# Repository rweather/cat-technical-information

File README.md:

Technical Information for the Dick Smith Cat / Laser 3000
=========================================================

This project was born out of nostalgia for the 6502-based "Dick Smith Cat"
computer that I had back in the 1980's.  It was mostly Apple II compatible;
overseas it was known as the VTech Laser 3000.  See **History** below for more.

Unfortunately the power supply died on mine and I sent it to the dump.
I now really wish I hadn't!  Fortunately, I did find a Cat on Gumtree
for sale in 2024 and so I now have a Cat again, together with some
accessories (joysticks, disk controller, disk drive, and emulator cartridge).

This project is my contribution to preserving Cat history.

## Schematics

The schematics in the original [Technical Reference Manual](https://archive.org/details/dsecattrm)
are very hard to read.  So I decided to redraw them in KiCad.

There are lots of details missing in the Technical Reference Manual;
for example, U17 is listed in the schematic but there is no information
that it is a 74LS86 Quad XOR gate.  It was necessary to figure out
from context what the components were.  I'll cross-check them with the
actual Cat later.

Here are the schematics, redrawn in Kicad:

* [Motherboard Schematic](schematics/Dick_Smith_Cat_Motherboard/PDF/Dick_Smith_Cat_Motherboard.pdf)
* [PAL Linear Board Schematic](schematics/Dick_Smith_Cat_Linear_Board_PAL/PDF/Dick_Smith_Cat_Linear_Board_PAL.pdf)
* [Power Supply Schematic](schematics/Dick_Smith_Cat_Power_Supply/PDF/Dick_Smith_Cat_Power_Supply.pdf)
* [Emulator Cartridge Schematic](schematics/Dick_Smith_Cat_Emulator/PDF/Dick_Smith_Cat_Emulator.pdf)
* [Joystick Schematic](schematics/Dick_Smith_Cat_Joysticks/PDF/Dick_Smith_Cat_Joysticks.pdf)

## Kernel ROM Listing

I have typed up the kernel ROM listing from the Technical Reference Manual,
and annotated it with my own notes as to what is happening.  The source
code can be found in the [src/kernel](src/kernel) directory.

## Memory Map

The Cat supports an 18-bit 256K memory address space, divided up into
sixteen 16K memory banks.  Any of these sixteen memory banks can be
mapped into four memory "windows" at addresses $0000, $4000, $8000, and
$C000.  By default the ROM maps memory banks 0, 1, 3, and F into the
four memory windows.

* $00000 to $0FFFF - 64K of RAM on the motherboard.
* $10000 to $2FFFF - 128K of expansion RAM (not fitted as standard).
* $30000 to $37FFF - Unused space.
* $38000 to $3BFFF - BASIC ROM.
* $3C000 to $3CFFF - I/O space.
* $3D000 to $3FFFF - BASIC and kernel monitor ROM.

The memory windows are set by writing the memory bank number (0-F) to the
I/O addresses $3C07C, $3C07D, $3C07E, and $3C07F.  The memory bank numbers
should also be written to zero page locations $C5, $C6, $C7, and $C8
so that the rest of the system knows the current memory arrangement.

Note: Writing a value other than F to $3C07F will make the system unusable
as the I/O space will become inaccessible in the 6502's 64K address space.
There is no way to restore the correct mapping except via a system reset.

## Slots

The Cat does not have physical slots in the same sense as the Apple II.
The 72-pin expansion connectors have the entire 256K 18-bit address bus and
8-bit data bus available.  Decoding of slot addresses is done on the plug-in
cartridges.  The I/O "slots" are virtual and are allocated as follows:

* Slot 0 - Emulator cartridge a.k.a the language card
* Slot 1 - Printer
* Slot 2 - RS-232
* Slot 3 - 80 column mode
* Slot 4 - Unused
* Slot 5 - Reserved for a second disk controller
* Slot 6 - Standard disk controller
* Slot 7 - Unused

At startup, the monitor ROM will probe for a disk controller in slot 6
and then the ROM will probe for a disk controller in slot 5.  If either
slot is occupied, the ROM jumps to the disk controller's ROM to boot
from the external disk drive.

Cat's didn't use slot 5 - the disk controller was always in slot 6.

Slot 5 could be used to create a bootable game or program cartridge.
Instead of booting a disk, the program in the cartridge is run
automatically at power on if there is no disk constroller cartridge
present.  The following hexadecimal bytes should appear at $C500 to
make the cartridge auto-boot:

    A2 20 A0 00 A2 03 86 3C

These signature bytes are followed by code to load the cartridge's ROM
contents into main RAM to run the program.  Or bank-switch in the
cartridge at address $4000 or $8000 to execute directly out of the ROM.

If a disk controller cartridge is present in slot 6, then slot 5 will not
boot automatically.  Use <tt>PR#5</tt> at the BASIC prompt to activate the
code in the slot 5 cartridge.

## New Projects

* [ROM cartridge for the RS-232 interface](ROMCart.md)

## Can We Rebuild It?

Since Cats (and Laser 3000's) are so rare these days, there is a question as
to whether we could build a replica using modern off-the-shelf parts.

Well, no.

The core of the Cat is two 64-pin gate array chips, U2 and U14.  These
handle glue logic, dynamic RAM interfacing, and the video subsystem.
Without a working Cat to harvest the chips from, there's no way to replicate it.
And if I have a working Cat, I don't need to replicate it!

The gate arrays and clean-roomed ROM's is how VTech avoided Apple's lawyers.
It wasn't a chip for chip rip-off of the Apple II like many other clones
back in the day.

In theory a new circuit could be built using the equivalent in TTL logic
chips, but then you'd end up with a straight Apple II clone.  There are
plenty of designs online for that, including the original Apple II schematics.

The other possibility is to use a modern FPGA to replicate the original
gate arrays on 64-pin carrier boards.  That would be useful for repairing
actual Cats, but would be a lot of work.

Another problem for replication is the ROM's.  The assembly code for the
kernel monitor ROM is in the Technical Reference Manual.  I have put the
code in the [src/kernel](src/kernel) sub-directory of this repository,
annotated with some of my own notes to explain what is going on.

I wasn't been able to find the BASIC ROM's online anywhere.  I had bits and
pieces of the BASIC ROM's that I disassembled by hand back in the day,
but not a complete set.  Now that I have a working Cat, I will dump the
ROM's at some point.

## Chip List

As mentioned above, the schematics in the Technical Reference Manual do not
include information as to what part each "Un" designator corresponds to.
Most of them I was able to figure out from context and the rest were
confirmed through inspection of an actual Cat motherboard.

<table border="1">
<tr><td><b>Designator</b></td><td><b>Part</b></td><td><b>Schematic Pages</b></td></tr>
<tr><td>U1</td><td>555 Timer</td><td>2</td></tr>
<tr><td>U2</td><td>Gate Array 2</td><td>4</td></tr>
<tr><td>U3</td><td>74LS04 Hex Inverter</td><td>4</td></tr>
<tr><td>U4</td><td>74LS04 Hex Inverter</td><td>2, 4, 7</td></tr>
<tr><td>U5</td><td>4164 64-kbit Dynamic RAM</td><td>5</td></tr>
<tr><td>U6</td><td>4164 64-kbit Dynamic RAM</td><td>5</td></tr>
<tr><td>U7</td><td>4164 64-kbit Dynamic RAM</td><td>5</td></tr>
<tr><td>U8</td><td>4164 64-kbit Dynamic RAM</td><td>5</td></tr>
<tr><td>U9</td><td>4164 64-kbit Dynamic RAM</td><td>5</td></tr>
<tr><td>U10</td><td>4164 64-kbit Dynamic RAM</td><td>5</td></tr>
<tr><td>U11</td><td>4164 64-kbit Dynamic RAM</td><td>5</td></tr>
<tr><td>U12</td><td>4164 64-kbit Dynamic RAM</td><td>5</td></tr>
<tr><td>U13</td><td>74LS174 Hex D-Type Flip-Flop (some boards fit a 74LS244 instead for U13)</td><td>4</td></tr>
<tr><td>U14</td><td>Gate Array 1</td><td>4</td></tr>
<tr><td>U15</td><td>74LS139 Dual 2-Line to 4-Line Decoder</td><td>5, 6</td></tr>
<tr><td>U16</td><td>74LS138 3-Line to 8-Line Decoder</td><td>6</td></tr>
<tr><td>U17</td><td>74LS86 Quad XOR Gate</td><td>2</td></tr>
<tr><td>U18</td><td>74LS74 Dual D Flip-Flop</td><td>7</td></tr>
<tr><td>U19</td><td>74LS125 Quad Buffer with Tri-State Outputs</td><td>2, 3, 7</td></tr>
<tr><td>U20</td><td>74LS08 Quad AND Gate</td><td>5, 7</td></tr>
<tr><td>U21</td><td>74LS163 Binary 4-bit Counter</td><td>2</td></tr>
<tr><td>U22</td><td>2732 EPROM (Character Generator)</td><td>7</td></tr>
<tr><td>U23</td><td>74LS166 Shift Register</td><td>7</td></tr>
<tr><td>U24</td><td>74LS244 Octal Buffer</td><td>3</td></tr>
<tr><td>U25</td><td>74LS244 Octal Buffer</td><td>3</td></tr>
<tr><td>U26</td><td>74LS244 Octal Buffer</td><td>3</td></tr>
<tr><td>U27</td><td>6502A CPU</td><td>3</td></tr>
<tr><td>U28</td><td>Not used in the schematic (some boards fit a 74LS04 for U28)</td><td> </td></tr>
<tr><td>U29</td><td>74LS74 Dual D Flip-Flop</td><td>7</td></tr>
<tr><td>U30</td><td>74LS00 Quad NAND Gate</td><td>7</td></tr>
<tr><td>U31</td><td>74LS74 Dual D Flip-Flop</td><td>2</td></tr>
<tr><td>U32</td><td>74LS374 Octal D-Type Latch, Edge Triggered</td><td>7</td></tr>
<tr><td>U33</td><td>74LS373 Octal D-Type Latch, Transparent</td><td>9</td></tr>
<tr><td>U34</td><td>74LS08 Quad AND Gate</td><td>2, 6, 10</td></tr>
<tr><td>U35</td><td>74LS00 Quad NAND Gate</td><td>3, 7</td></tr>
<tr><td>U36</td><td>74LS04 Hex Inverter</td><td>2, 3, 6, 7</td></tr>
<tr><td>U37</td><td>74LS145 BCD to decimal decoder, open collector</td><td>8</td></tr>
<tr><td>U38</td><td>27256 28-pin ROM</td><td>6</td></tr>
<tr><td>U39</td><td>74LS374 Octal D-Type Latch, Edge Triggered</td><td>10</td></tr>
<tr><td>U40</td><td>74LS245 Bus Transceiver</td><td>3</td></tr>
<tr><td>U41</td><td>74LS244 Octal Buffer</td><td>8</td></tr>
<tr><td>U42</td><td>SN76489AN Sound Generator</td><td>10</td></tr>
<tr><td>U43</td><td>74LS138 3-Line to 8-Line Decoder</td><td>10</td></tr>
<tr><td>U44</td><td>8048 Keyboard Microcontroller</td><td>8</td></tr>
<tr><td>U45</td><td>74LS251 8-Line to 1-Line Selector/Muliplexer</td><td>10</td></tr>
<tr><td>U46</td><td>558 Quad Timer</td><td>10</td></tr>
<tr><td> </td><td> </td><td> </td></tr>
<tr><td>U47</td><td>74LS00 Quad NAND Gate</td><td>Linear Board 1</td></tr>
<tr><td>U48</td><td>TEA 1002 PAL Encoder</td><td>Linear Board 1</td></tr>
<tr><td>U49</td><td>uA741C Amplifier</td><td>Linear Board 2</td></tr>
<tr><td>U50</td><td>TBA820M Amplifier</td><td>Linear Board 3</td></tr>
</table>

## References

* [Cat Technical Reference Manual on archive.org](https://archive.org/details/dsecattrm)
* [Laser 3000 Personal Computer User's Manual on archive.org](https://archive.org/details/l3000UM)
* [Laser 3000 Personal Computer BASIC Reference Manual on archive.org](https://archive.org/details/Laser3000PersonalComputerBASICReferenceManualAppleIIClone)
* [Dick Smith Cat on Reddit](https://www.reddit.com/r/retrobattlestations/comments/tohbjp/team_green_dick_smith_cat_aka_vtech_laser_3000/)
* [Dick Smith Cat on AppleLogic](http://www.applelogic.org/TheCAT.html)
* [Laser 3000 on OLD-COMPUTERS.COM](https://www.old-computers.com/museum/computer.asp?c=156)

## History

The Dick Smith Cat was the first computer that my family owned.  My parents
paid AUD$699 for it in 1984 when I would have been about 14 years old.
The receipt was still stapled into the back of one of the manuals!
The family's black and white spare holiday TV served as the monitor.
Later a printer and a disk drive were added.

Overseas, the Cat was known as the VTech Laser 3000.  Dick Smith Electronics
rebadged it as the "Cat" in Australia.  It was mostly Apple II compatible
but about half the price that an Apple II was at the time.

The power supply died around 1988 or 1989 and it never recovered.
I sent it to the electronics recyclers a long time ago, and now I
wish I hadn't.  Knowing what I do now, it may have been possible to
restore it.

Back in the day I quickly discovered that the ROM listings only
contained a tiny fraction of all of the ROM's in the system.
But that didn't stop me!  I disassembled a lot of the original ROM's by
hand on paper while still in high school.  And I still have my hand-written
notes up in the cupboard!

The original process of disassembly was made more difficult because the
Cat's kernel monitor did not have a disassembler like the Apple II did.
I had to memorise the entire 6502 instruction set and decode the
hexadecimal by hand.

My hand-written notes are incomplete but I do have a large chunk of the
original BASIC ROM's in my notes.

## License

<p xmlns:cc="http://creativecommons.org/ns#" xmlns:dct="http://purl.org/dc/terms/"><span property="dct:title">Schematics for Dick Smith Cat</span> by <span property="cc:attributionName">Rhys Weatherley</span> is licensed under <a href="http://creativecommons.org/licenses/by-nc-sa/4.0/?ref=chooser-v1" target="_blank" rel="license noopener noreferrer" style="display:inline-block;">Attribution-NonCommercial-ShareAlike 4.0 International</a></p>

## Contact

For more information on this code, to report bugs, or to suggest
improvements, please contact the author Rhys Weatherley via
[email](mailto:rhys.weatherley@gmail.com).

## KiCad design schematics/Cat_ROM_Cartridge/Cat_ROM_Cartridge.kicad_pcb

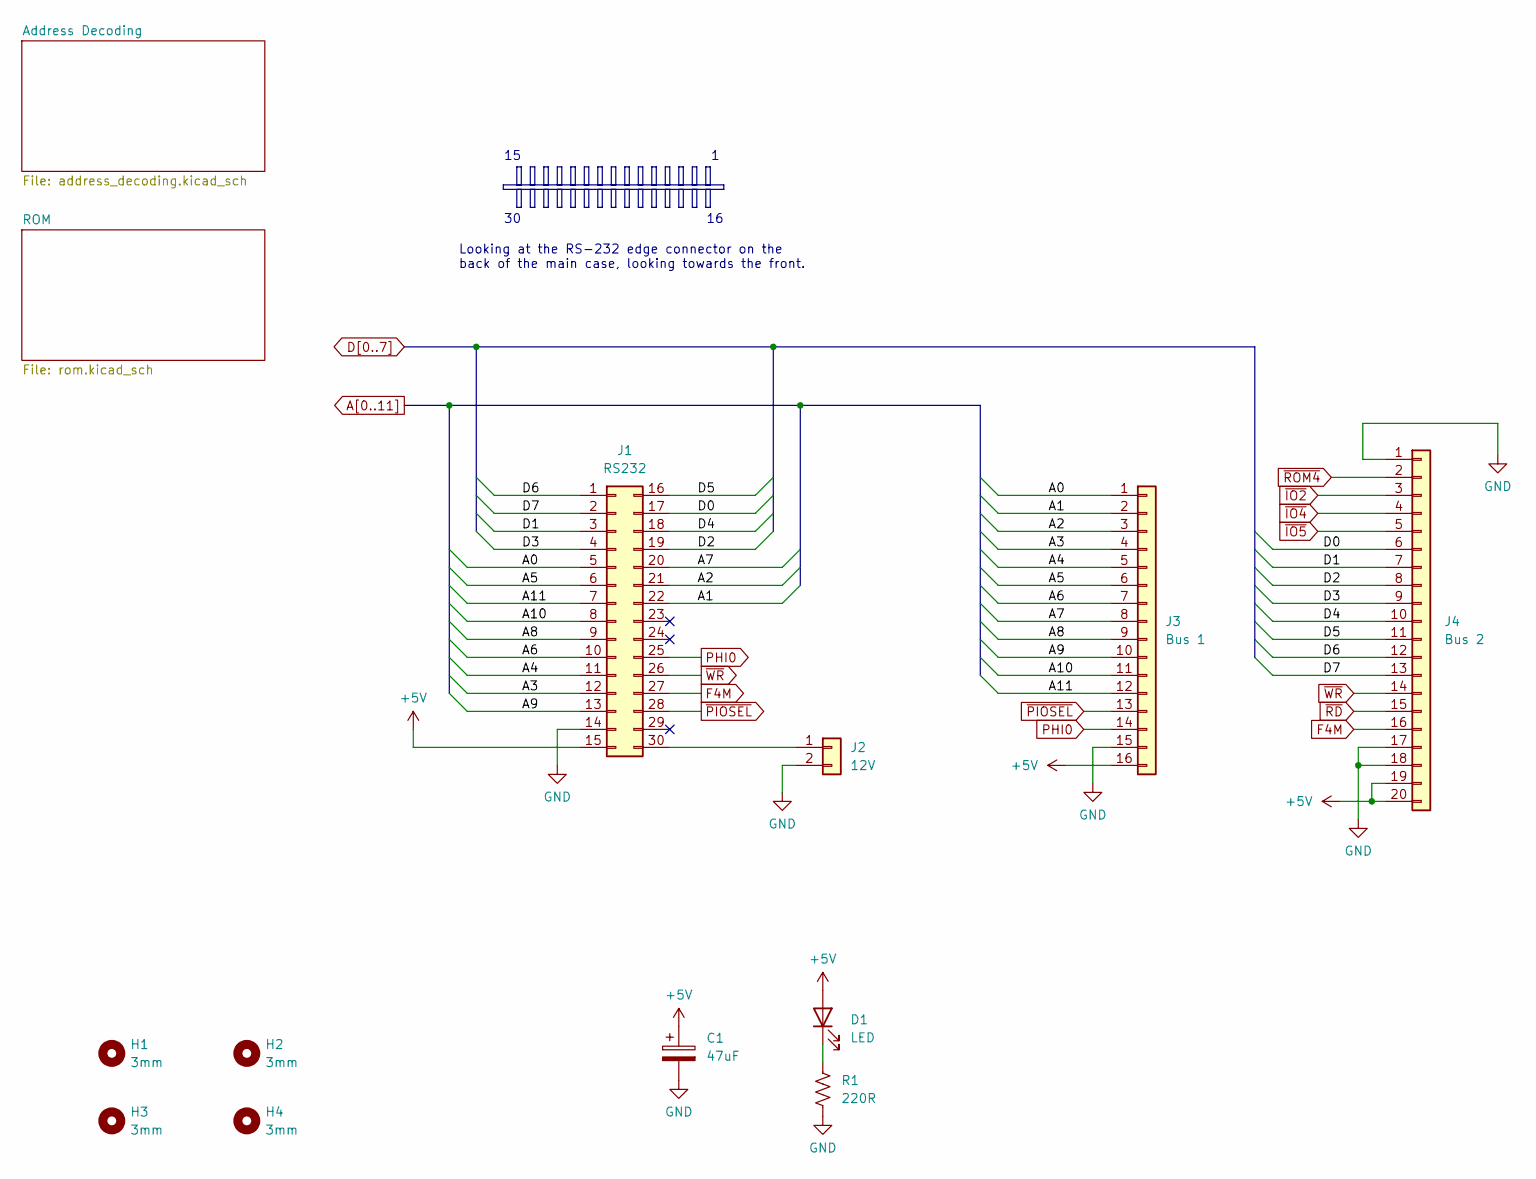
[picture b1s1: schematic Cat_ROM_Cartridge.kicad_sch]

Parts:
C1: 47uF; CP_Radial_D6.3mm_P2.50mm
D1: LED; LED_D3.0mm
H1, H2, H3, H4: 3mm; MountingHole_3mm
J1: RS232; Edge_Connector_30pin
J2: 12V; PinHeader_1x02_P2.54mm_Vertical
J3: Bus 1; PinSocket_1x16_P2.54mm_Vertical
J4: Bus 2; PinSocket_1x20_P2.54mm_Vertical
R1: 220R; R_Axial_DIN0207_L6.3mm_D2.5mm_P7.62mm_Horizontal

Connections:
+5V: C1.1, D1.2 (A), J1.15, J3.16, J4.19, J4.20; also elsewhere on the board
A0: J1.5, J3.1; also elsewhere on the board
A1: J1.22, J3.2; also elsewhere on the board
A2: J1.21, J3.3; also elsewhere on the board
A3: J1.12, J3.4; also elsewhere on the board
A4: J1.11, J3.5; also elsewhere on the board
A5: J1.6, J3.6; also elsewhere on the board
A6: J1.10, J3.7; also elsewhere on the board
A7: J1.20, J3.8; also elsewhere on the board
A8: J1.9, J3.9; also elsewhere on the board
A9: J1.13, J3.10; also elsewhere on the board
A10: J1.8, J3.11; also elsewhere on the board
A11: J1.7, J3.12; also elsewhere on the board
D0: J1.17, J4.6; also elsewhere on the board
D1: J1.3, J4.7; also elsewhere on the board
D2: J1.19, J4.8; also elsewhere on the board
D3: J1.4, J4.9; also elsewhere on the board
D4: J1.18, J4.10; also elsewhere on the board
D5: J1.16, J4.11; also elsewhere on the board
D6: J1.1, J4.12; also elsewhere on the board
D7: J1.2, J4.13; also elsewhere on the board
F4M: J1.27, J4.16
GND: C1.2, J1.14, J2.2, J3.15, J4.1, J4.17, J4.18, R1.2; also elsewhere on the board
unnamed: D1.1 (K), R1.1
unnamed: J1.30, J2.1
PHI0: J1.25, J3.14; also elsewhere on the board
~IO2: J4.3; also elsewhere on the board
~IO4: J4.4; also elsewhere on the board
~IO5: J4.5; also elsewhere on the board
~PIOSEL: J1.28, J3.13; also elsewhere on the board
~RD: J4.15; also elsewhere on the board
~ROM4: J4.2; also elsewhere on the board
~WR: J1.26, J4.14; also elsewhere on the board

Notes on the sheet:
Looking at the RS-232 edge connector on the back of the main case, looking towards the front.

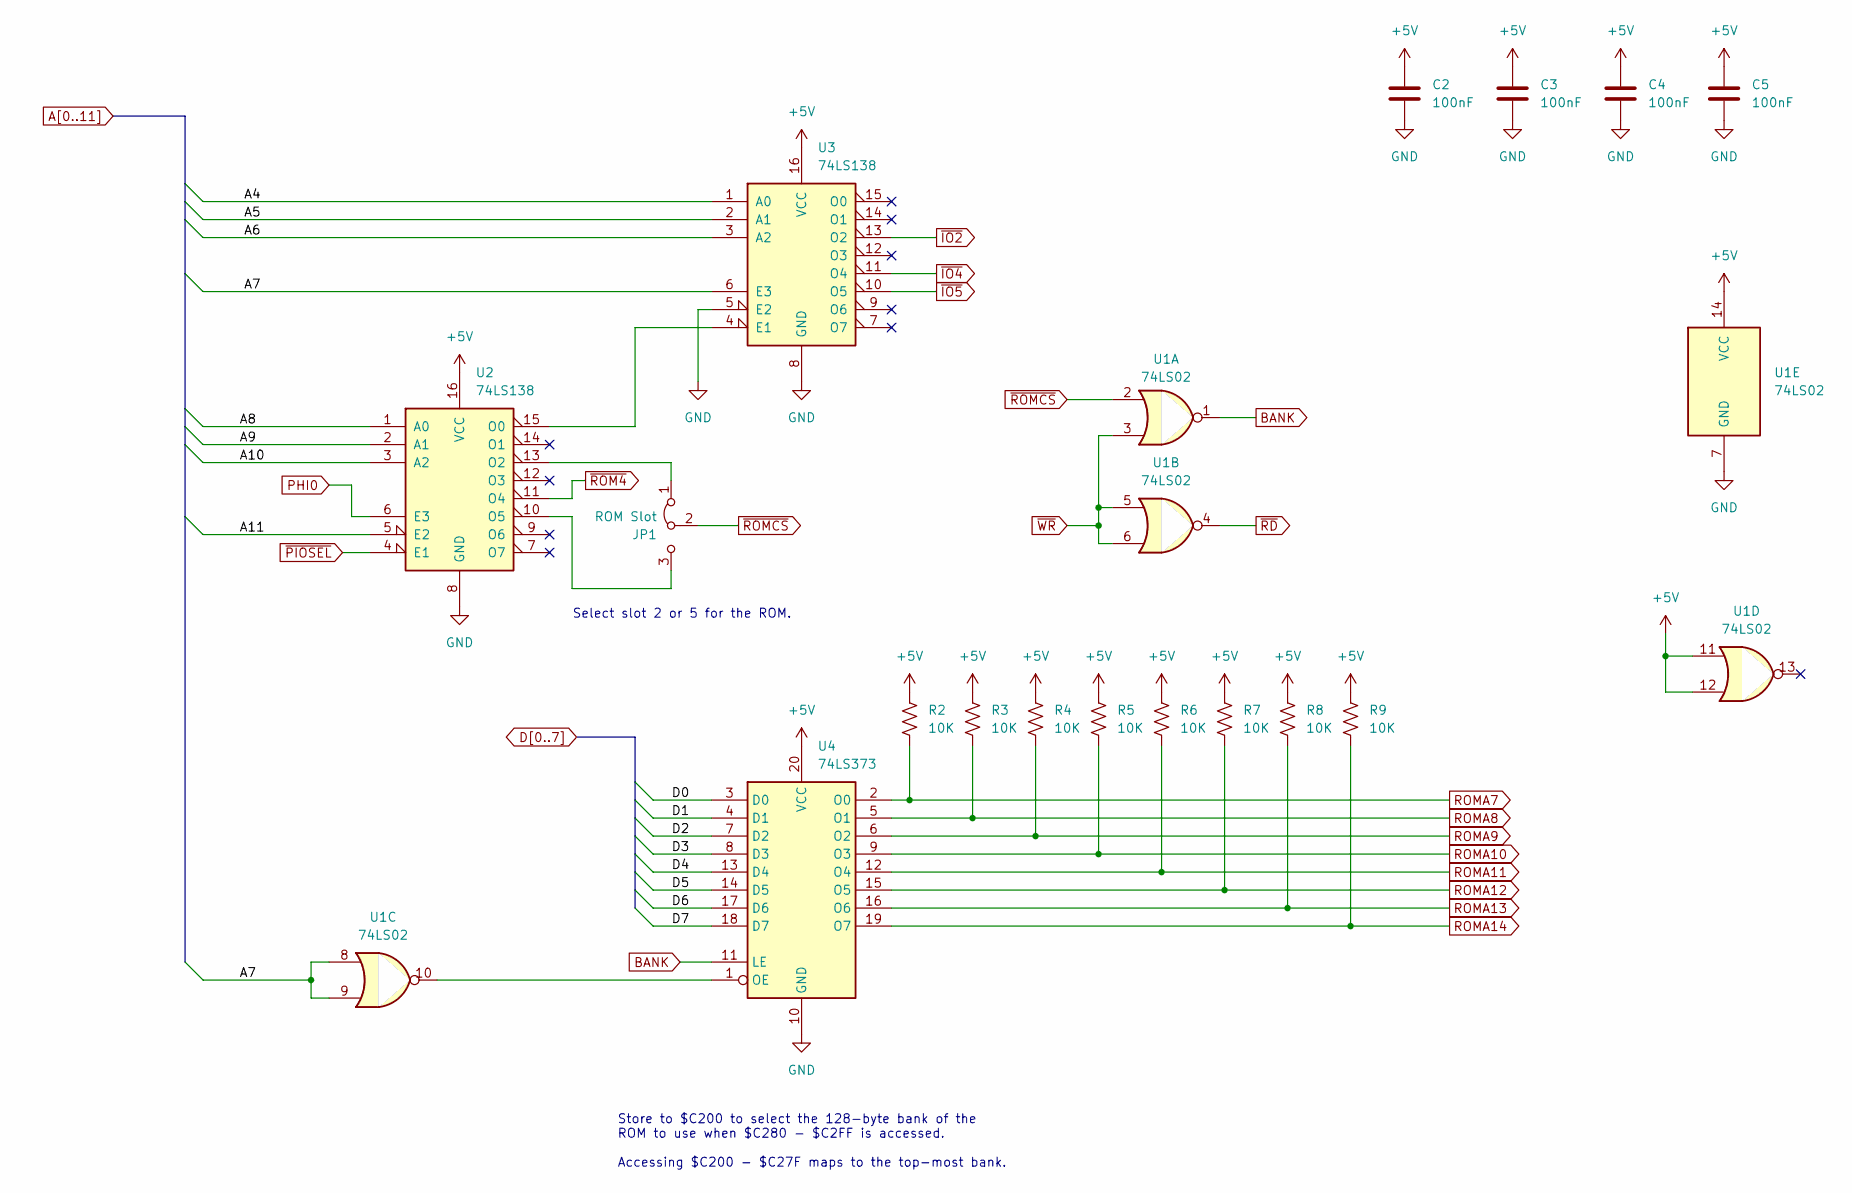
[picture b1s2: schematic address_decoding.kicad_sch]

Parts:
C2, C3, C4, C5: 100nF; C_Disc_D5.0mm_W2.5mm_P5.00mm
JP1: ROM Slot; PinHeader_1x03_P2.54mm_Vertical
R2, R3, R4, R5, R6, R7, R8, R9: 10K; R_Axial_DIN0207_L6.3mm_D2.5mm_P7.62mm_Horizontal
U1: 74LS02; DIP-14_W7.62mm
U2, U3: 74LS138; DIP-16_W7.62mm
U4: 74LS373; DIP-20_W7.62mm

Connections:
+5V: C2.1, C3.1, C4.1, C5.1, R2.1, R3.1, R4.1, R5.1, R6.1, R7.1, R8.1, R9.1, U1.11, U1.12, U1.14 (VCC), U2.16 (VCC), U3.16 (VCC), U4.20 (VCC); also elsewhere on the board
A4: U3.1 (A0); also elsewhere on the board
A5: U3.2 (A1); also elsewhere on the board
A6: U3.3 (A2); also elsewhere on the board
A7: U1.8, U1.9, U3.6 (E3); also elsewhere on the board
A8: U2.1 (A0); also elsewhere on the board
A9: U2.2 (A1); also elsewhere on the board
A10: U2.3 (A2); also elsewhere on the board
A11: U2.5 (E2); also elsewhere on the board
BANK: U1.1, U4.11 (LE)
D0: U4.3 (D0); also elsewhere on the board
D1: U4.4 (D1); also elsewhere on the board
D2: U4.7 (D2); also elsewhere on the board
D3: U4.8 (D3); also elsewhere on the board
D4: U4.13 (D4); also elsewhere on the board
D5: U4.14 (D5); also elsewhere on the board
D6: U4.17 (D6); also elsewhere on the board
D7: U4.18 (D7); also elsewhere on the board
GND: C2.2, C3.2, C4.2, C5.2, U1.7 (GND), U2.8 (GND), U3.5 (E2), U3.8 (GND), U4.10 (GND); also elsewhere on the board
unnamed: JP1.1 (A), U2.13 (O2)
unnamed: JP1.3 (B), U2.10 (O5)
unnamed: U2.15 (O0), U3.4 (E1)
unnamed: U1.10, U4.1 (OE)
PHI0: U2.6 (E3); also elsewhere on the board
ROMA7: R2.2, U4.2 (O0); also elsewhere on the board
ROMA8: R3.2, U4.5 (O1); also elsewhere on the board
ROMA9: R4.2, U4.6 (O2); also elsewhere on the board
ROMA10: R5.2, U4.9 (O3); also elsewhere on the board
ROMA11: R6.2, U4.12 (O4); also elsewhere on the board
ROMA12: R7.2, U4.15 (O5); also elsewhere on the board
ROMA13: R8.2, U4.16 (O6); also elsewhere on the board
ROMA14: R9.2, U4.19 (O7); also elsewhere on the board
~IO2: U3.13 (O2); also elsewhere on the board
~IO4: U3.11 (O4); also elsewhere on the board
~IO5: U3.10 (O5); also elsewhere on the board
~PIOSEL: U2.4 (E1); also elsewhere on the board
~RD: U1.4; also elsewhere on the board
~ROM4: U2.11 (O4); also elsewhere on the board
~ROMCS: JP1.2 (C), U1.2; also elsewhere on the board
~WR: U1.3, U1.5, U1.6; also elsewhere on the board

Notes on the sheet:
Store to $C200 to select the 128-byte bank of the ROM to use when $C280 - $C2FF is accessed. Accessing $C200 - $C27F maps to the top-most bank.
Select slot 2 or 5 for the ROM.

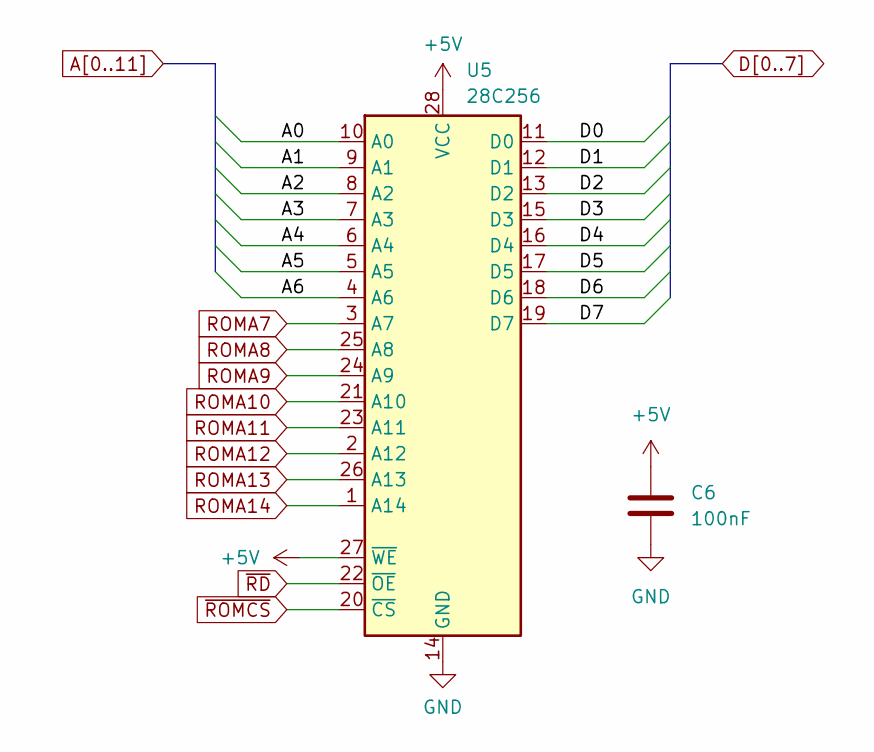
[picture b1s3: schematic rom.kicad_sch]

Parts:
C6: 100nF; C_Disc_D5.0mm_W2.5mm_P5.00mm
U5: 28C256; DIP_Socket-28_W11.9_W12.7_W15.24_W17.78_W18.5_3M_228-1277-0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

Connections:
+5V: C6.1, U5.27 (~WE), U5.28 (VCC); also elsewhere on the board
A0: U5.10 (A0); also elsewhere on the board
A1: U5.9 (A1); also elsewhere on the board
A2: U5.8 (A2); also elsewhere on the board
A3: U5.7 (A3); also elsewhere on the board
A4: U5.6 (A4); also elsewhere on the board
A5: U5.5 (A5); also elsewhere on the board
A6: U5.4 (A6); also elsewhere on the board
D0: U5.11 (D0); also elsewhere on the board
D1: U5.12 (D1); also elsewhere on the board
D2: U5.13 (D2); also elsewhere on the board
D3: U5.15 (D3); also elsewhere on the board
D4: U5.16 (D4); also elsewhere on the board
D5: U5.17 (D5); also elsewhere on the board
D6: U5.18 (D6); also elsewhere on the board
D7: U5.19 (D7); also elsewhere on the board
GND: C6.2, U5.14 (GND); also elsewhere on the board
ROMA7: U5.3 (A7); also elsewhere on the board
ROMA8: U5.25 (A8); also elsewhere on the board
ROMA9: U5.24 (A9); also elsewhere on the board
ROMA10: U5.21 (A10); also elsewhere on the board
ROMA11: U5.23 (A11); also elsewhere on the board
ROMA12: U5.2 (A12); also elsewhere on the board
ROMA13: U5.26 (A13); also elsewhere on the board
ROMA14: U5.1 (A14); also elsewhere on the board
~RD: U5.22 (~OE); also elsewhere on the board
~ROMCS: U5.20 (~CS); also elsewhere on the board

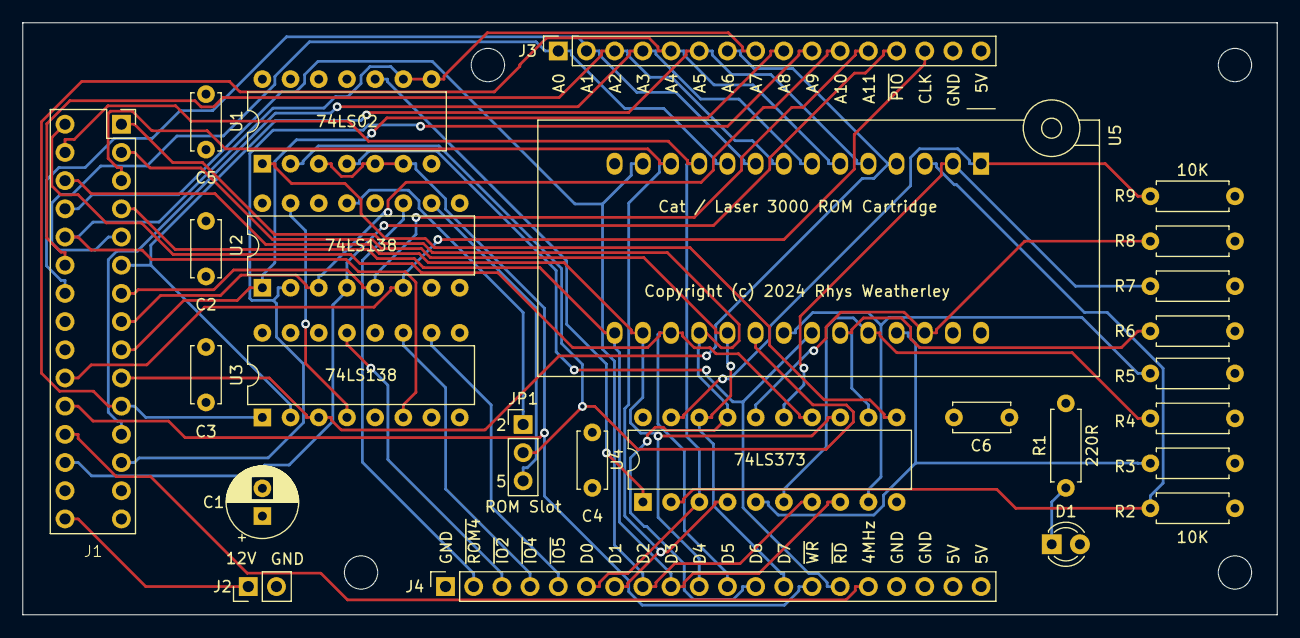
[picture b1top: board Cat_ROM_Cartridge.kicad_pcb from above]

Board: 4 copper layers, 113.0 x 53.3 mm, 30 parts (0 on the bottom side), 47 nets.

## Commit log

2024-05-05 Schematics for Dick Smith Cat Motherboard
2024-05-05 Kernel source code
2024-07-03 Schematic for the PAL Linear Board
2024-07-06 Power supply schematic
2024-07-06 README updates
2024-07-13 Schematic for emulator cartridge
2024-07-13 Schematic for the joysticks
2024-07-30 Update README.md - I have a real Cat now!
2024-07-30 Add pinout for composite video connector on linear board
2024-08-02 Disk controller ROM
2024-08-02 Document the memory map and slots
2024-08-02 Update emulator schematic upon inspection of board
2024-08-03 Fix chip numbers in the motherboard schematic
2024-08-20 Disassembly of the printer driver ROM in slot #1
2024-08-20 Add more connector pinouts to the schematics
2024-08-20 Assembly listings for the ROM sources
2024-09-01 ROM cartridge for the RS232 expansion connector
2024-09-14 Documentation and code for the ROM cartridge
2024-09-14 Simple method to load BASIC programs from EEPROM
2024-09-28 OE and W were swapped in the emulator schematic - fix them
2026-04-09 Fix pinout of SN76489AN sound chip
    The sound chip uses D0 as the MSB. The bits are swapped in hardware.

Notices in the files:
schematics/Cat_ROM_Cartridge/Cat_ROM_Cartridge.kicad_pcb:
Copyright (c) 2024 Rhys Weatherley
